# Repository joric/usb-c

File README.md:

# USB-C

My collection of USB Type-C converter boards

See project wiki: https://github.com/joric/usb-c/wiki

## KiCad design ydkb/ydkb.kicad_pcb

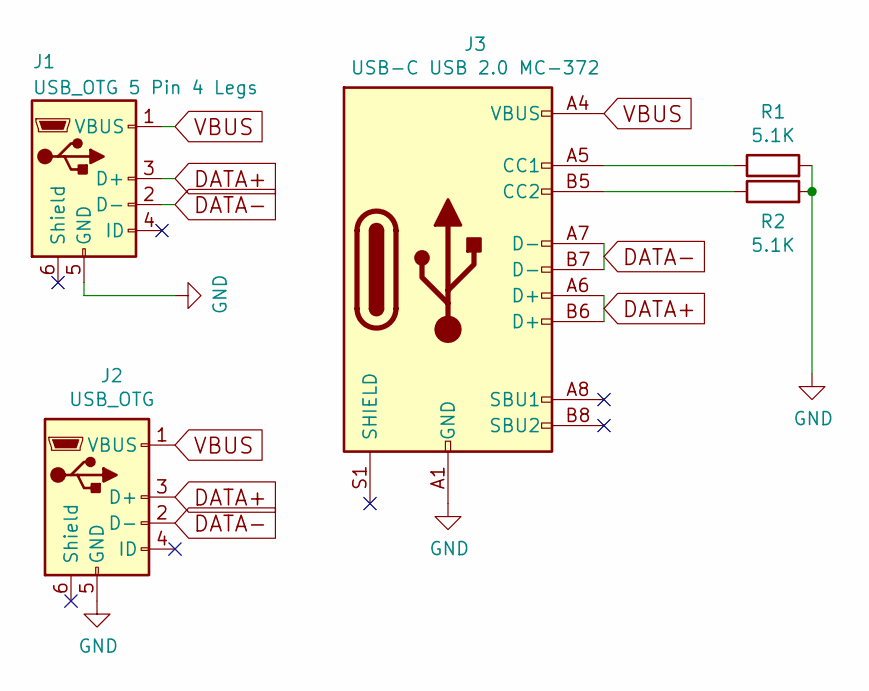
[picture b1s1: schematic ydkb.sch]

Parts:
J1: USB_OTG 5 Pin 4 Legs; usb_micro
J2: USB_OTG; SMD_USB_Mini_B_Female_548190519
J3: USB-C USB 2.0 MC-372; usb_type_c
R1, R2: 5.1K; R_0603_1608Metric

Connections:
DATA+: J1.3 (D+), J2.3 (D+), J3.A6 (D+), J3.B6 (D+)
DATA-: J1.2 (D-), J2.2 (D-), J3.A7 (D-), J3.B7 (D-)
GND: J1.5 (GND), J2.5 (GND), J3.A1 (GND), J3.A12 (GND), J3.B1 (GND), J3.B12 (GND), R1.2, R2.2
unnamed: J3.A5 (CC1), R1.1
unnamed: J3.B5 (CC2), R2.1
VBUS: J1.1 (VBUS), J2.1 (VBUS), J3.A4 (VBUS), J3.A9 (VBUS), J3.B4 (VBUS), J3.B9 (VBUS)

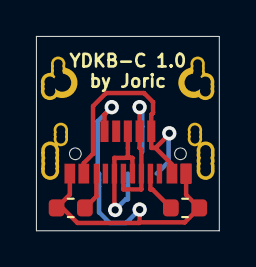
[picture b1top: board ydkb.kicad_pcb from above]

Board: 2 copper layers, 10.2 x 10.8 mm, 5 parts (0 on the bottom side), 6 nets.

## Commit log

2019-12-12 added gerbers
2019-12-22 Added unlicense
2020-12-09 added original gerbers
